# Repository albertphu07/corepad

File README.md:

# corepad
# Updated Official STL Files here https://github.com/albertphu07/CoreCase 
The corepad is a  macro pad designed to combine keybinds into s single key. The project runs on the Seeed Studio XIAO RP2040 microcontroller and uses KMK Firmware built with CircuitPython.

## Key Features

* many sperate layers (your choice).
* OLED display to show the active mode.
* Open-source code using KMK, allowing quick modifications without needing to compile firmware.

# Bill of Materials (BOM)

| Qty | Part | Effective Cost |
|------|------|------:|
| 1x | Seeed XIAO RP2040 (un-Soldered) | $10.00 |
| 1x | 0.91" OLED Display  | ~$4.00 |
| 3x | White Blank DSA Keycaps | $0.99|
| 4x | M3x5mmx4mm Heat-Set Inserts | ~$0.99 |
| 1x | PCB | $6.32 	 | (With shipping (idk how much with customs fees due to tarffis and import from china))
| 1x | Soldering Iron | $9.99 | 
| 3x | Holy Panda Switches | 0.621 |
| 6x | HOLTITE | 5.59 | 
| | **Effective Build Cost Before Tax** | **~$37.88* |

**Notes**
- All listed parts currently have free shipping (execpt for pcb).
- Keycaps can be substituted with 3D-printed versions to reduce cost.
- PCB will be brought from jlbpcb or  OSHPARK
- Prices are subject to change due to shipping fees and tax
- Materials Needed: 3x Switches, 1X Seed XIAO RP2040, 1x OLED DISPLAY, 3x White Blank DSA Keycaps, 4x brass heated inserts, 4x Screws for the heated inserts!
- I Know That corepad V1 Documentation is a little crap but once i start working on the firmware a bit more ill clean it up later on :)

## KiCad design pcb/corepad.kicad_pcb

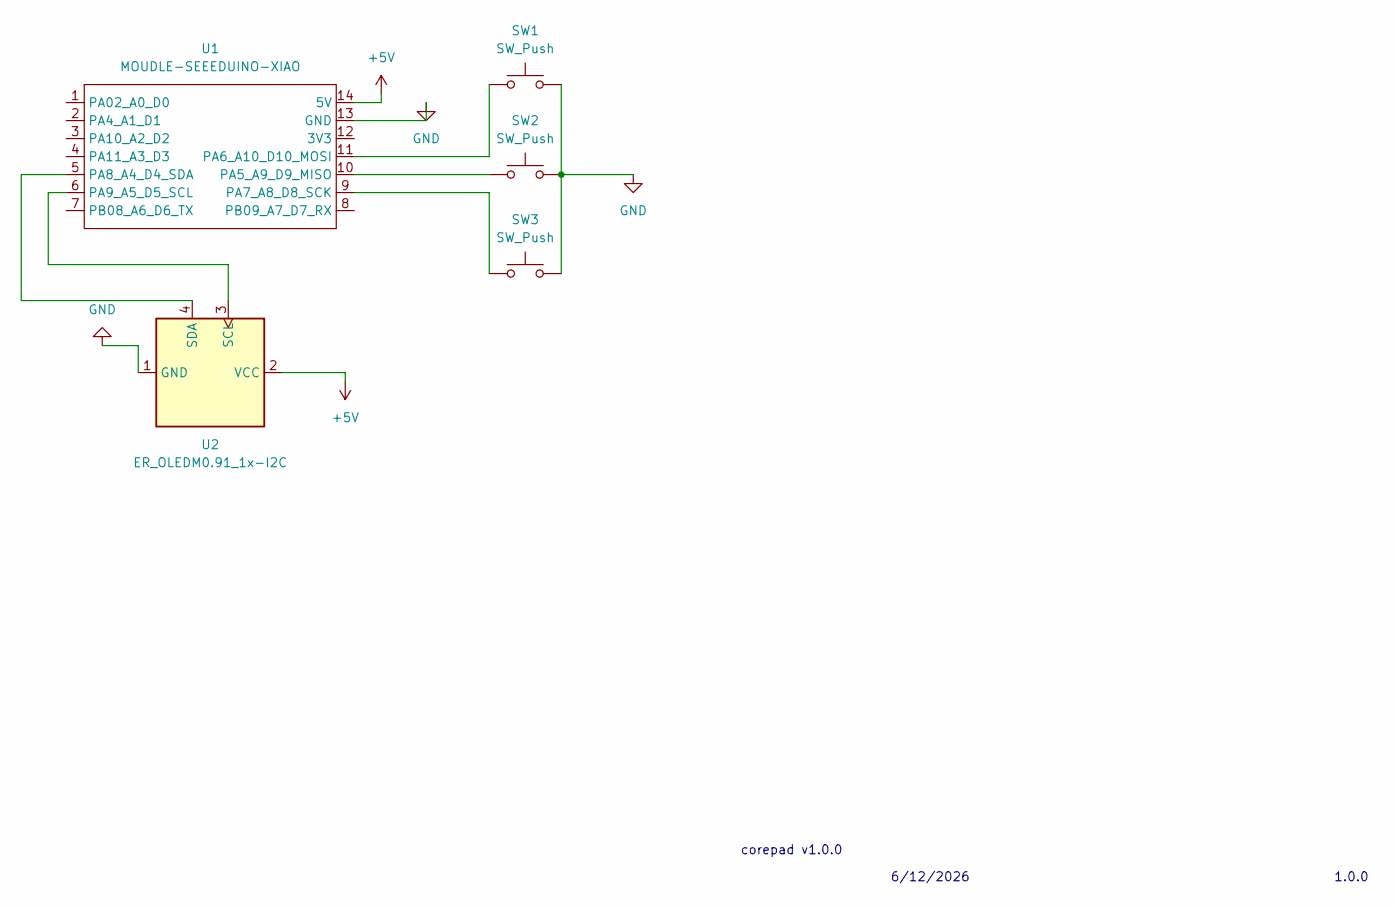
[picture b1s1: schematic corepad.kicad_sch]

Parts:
SW1, SW2, SW3: SW_Push; SW_Cherry_MX_1.00u_PCB
U1: MOUDLE-SEEEDUINO-XIAO; XIAO-Generic-Hybrid-14P-2.54-21X17.8MM
U2: ER_OLEDM0.91_1x-I2C

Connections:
+5V: U1.14 (5V), U2.2 (VCC)
GND: SW1.2, SW2.2, SW3.2, U1.13 (GND), U2.1 (GND)
unnamed: SW2.1, U1.10 (PA5_A9_D9_MISO)
unnamed: SW1.1, U1.11 (PA6_A10_D10_MOSI)
unnamed: SW3.1, U1.9 (PA7_A8_D8_SCK)
unnamed: U1.5 (PA8_A4_D4_SDA), U2.4 (SDA)
unnamed: U1.6 (PA9_A5_D5_SCL), U2.3 (SCL)

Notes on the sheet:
6/12/2026
1.0.0
corepad v1.0.0

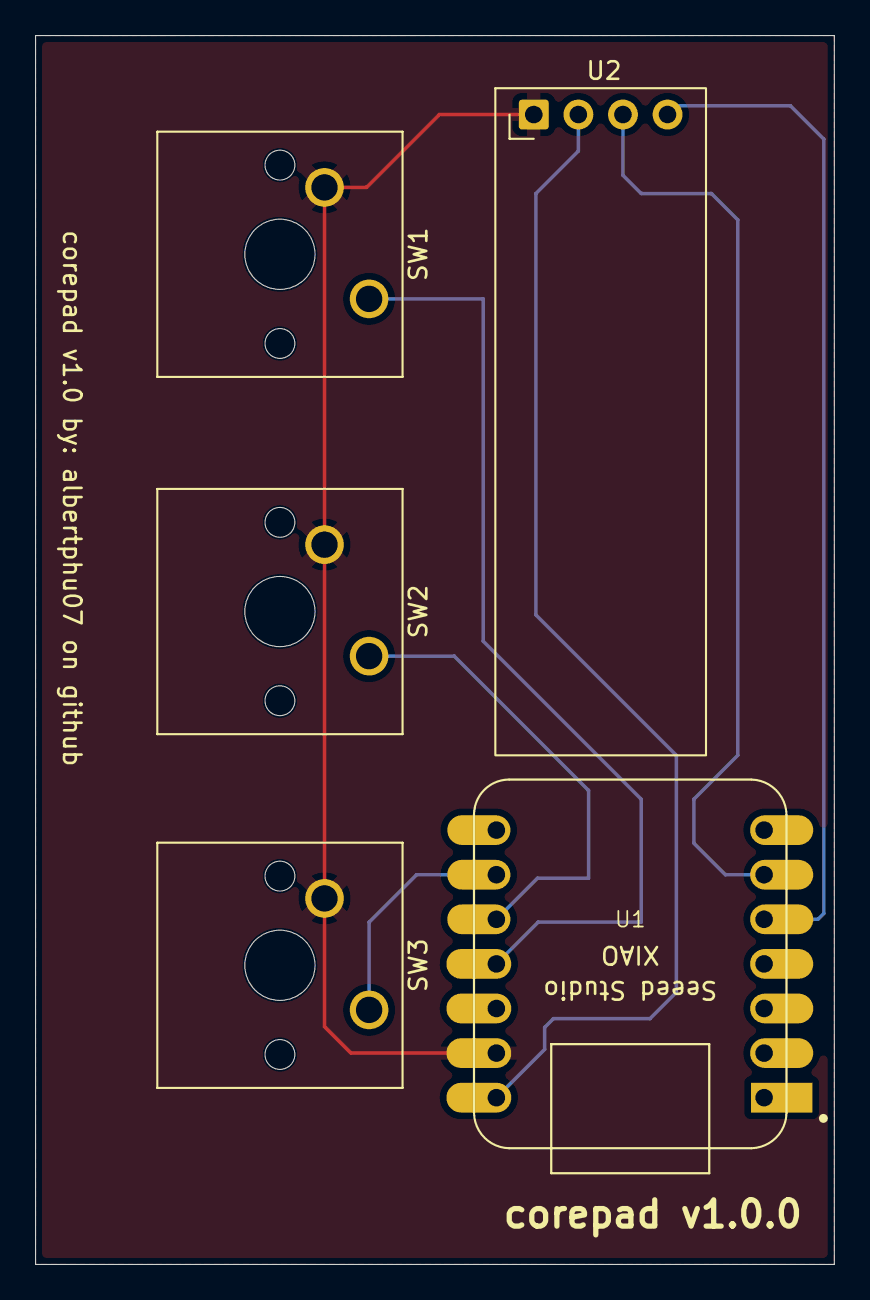
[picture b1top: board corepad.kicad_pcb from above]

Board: 2 copper layers, 45.5 x 70.0 mm, 5 parts (0 on the bottom side), 7 nets.

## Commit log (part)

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2026-06-12 Rename hackpad.kicad_prl to pcb/hackpad.kicad_prl
2026-06-12 Rename ~hackpad.kicad_pcb.lck to pcb/~hackpad.kicad_pcb.lck
2026-06-12 Rename Screenshot 2026-06-12 155300.png to assets/chematic.png
2026-06-12 Rename Screenshot 2026-06-12 155321.png to assets/pcb.png
2026-06-12 Rename hackpad.kicad_pcb to corepad.kicad_pcb
2026-06-12 Rename hackpad.kicad_prl to corepad.kicad_prl
2026-06-12 Rename hackpad.kicad_pro to corepad.kicad_pro
2026-06-12 Rename hackpad.kicad_sch to corepad.kicad_sch
2026-06-12 Rename gerbers.zip to production/gerbers.zip
2026-06-12 Rename Body1.stl to cad/bottom.stl
2026-06-12 Rename Body2.stl to cad/top.stl
2026-06-12 Rename Screenshot 2026-06-12 181028.png to model.png
2026-06-12 Rename chematic.png to schematic.png
2026-06-14 Rename Screenshot 2026-06-14 094703.png to pcb.png
2026-06-14 Create BOM.csv with component details
    Added a Bill of Materials (BOM) with components, quantities, and prices.
2026-06-14 Rename Screenshot 2026-06-14 102411.png to model.png
2026-06-14 Rename Screenshot 2026-06-14 102635.png to model.png
2026-06-14 Create LICENSE
2026-06-15 Rename gerbersv2.zip to gerbers.zip
2026-06-15 Rename corepad.f3d to corepadbase.f3d
2026-06-15 Rename corepad.step to corepadbase.step
2026-06-15 Rename Screenshot 2026-06-15 142547.png to model.png
2026-06-15 Rename Screenshot 2026-06-15 142547.png to model2.png
2026-06-15 Rename image.webp to pcb2.webp
2026-06-30 Add M3x16mm screws to BOM
